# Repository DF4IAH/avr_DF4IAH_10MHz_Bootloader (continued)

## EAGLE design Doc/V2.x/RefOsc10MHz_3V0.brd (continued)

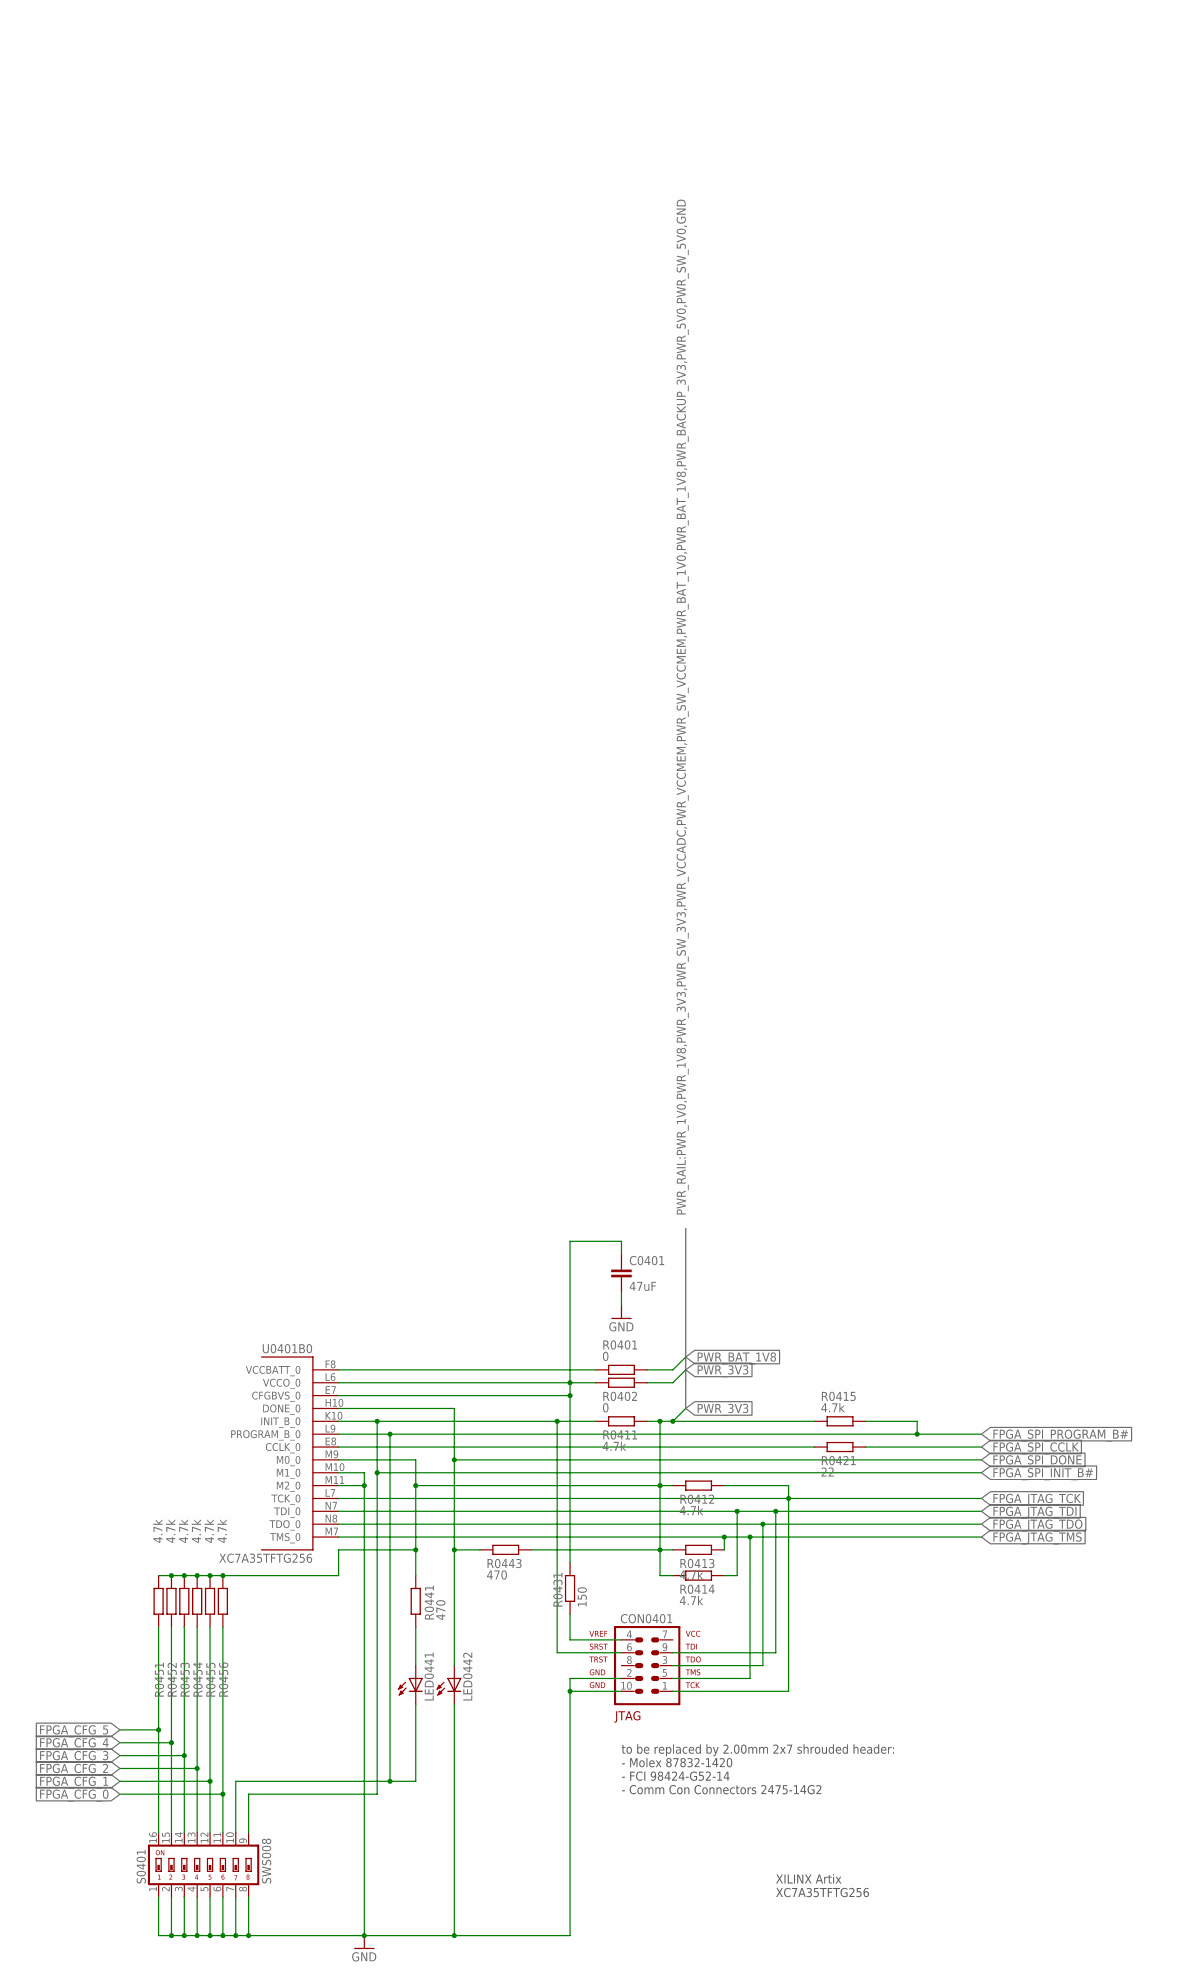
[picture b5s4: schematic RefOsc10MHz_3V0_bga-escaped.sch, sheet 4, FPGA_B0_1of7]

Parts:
C0401: 47uF; C0805
CON0401: AVR-JTAG-10SMD; 2X5SMD
LED0441, LED0442: LED; SMARTLED-TTW
R0401, R0402: 0; R0402
R0411, R0412, R0413, R0414, R0415, R0451, R0452, R0453, R0454, R0455, R0456: 4.7k; R0805
R0421: 22; R0805
R0431: 150; R0805
R0441, R0443: 470; R0805
S0401: SWS008; SMS-008
U0401: XC7A35TFTG256; FTG256_0MM4

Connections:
FPGA_CCLK_INTERN: R0421.1, U0401.E8 (CCLK_0)
FPGA_CFG_0: R0456.1, S0401.11; also elsewhere on the board
FPGA_CFG_1: R0455.1, S0401.12; also elsewhere on the board
FPGA_CFG_2: R0454.1, S0401.13; also elsewhere on the board
FPGA_CFG_3: R0453.1, S0401.14; also elsewhere on the board
FPGA_CFG_4: R0452.1, S0401.15; also elsewhere on the board
FPGA_CFG_5: R0451.1, S0401.16; also elsewhere on the board
FPGA_JTAG_TCK: CON0401.1, R0412.2, U0401.L7 (TCK_0)
FPGA_JTAG_TDI: CON0401.9, R0414.2, U0401.N7 (TDI_0)
FPGA_JTAG_TDO: CON0401.3, U0401.N8 (TDO_0)
FPGA_JTAG_TMS: CON0401.5, R0413.2, U0401.M7 (TMS_0)
FPGA_SPI_CCLK: R0421.2; also elsewhere on the board
FPGA_SPI_DONE: LED0442.A@1 (A), R0443.1, U0401.H10 (DONE_0)
FPGA_SPI_INIT_B#: CON0401.6, R0411.1, S0401.9, U0401.K10 (INIT_B_0)
FPGA_SPI_PROGRAM_B#: LED0441.C@1 (C), R0415.2, S0401.10, U0401.L9 (PROGRAM_B_0)
FPGA_VCCBATT: R0401.1, U0401.F8 (VCCBATT_0)
FPGA_VCCO_0: C0401.1, R0402.1, R0431.2, U0401.E7 (CFGBVS_0), U0401.L6 (VCCO_0)
GND: C0401.2, CON0401.2, CON0401.10, LED0442.C@1 (C), S0401.1, S0401.2, S0401.3, S0401.4, S0401.5, S0401.6, S0401.7, S0401.8, U0401.M10 (M1_0), U0401.M11 (M2_0); also elsewhere on the board
unnamed: LED0441.A@1 (A), R0441.1
unnamed: CON0401.4, R0431.1
PWR_3V3: R0402.2, R0411.2, R0412.1, R0413.1, R0414.1, R0415.1, R0441.2, R0443.2, R0451.2, R0452.2, R0453.2, R0454.2, R0455.2, R0456.2, U0401.M9 (M0_0); also elsewhere on the board
PWR_BAT_1V8: R0401.2; also elsewhere on the board

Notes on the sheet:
XILINX Artix XC7A35TFTG256
to be replaced by 2.00mm 2x7 shrouded header: - Molex 87832-1420 - FCI 98424-G52-14 - Comm Con Connectors 2475-14G2

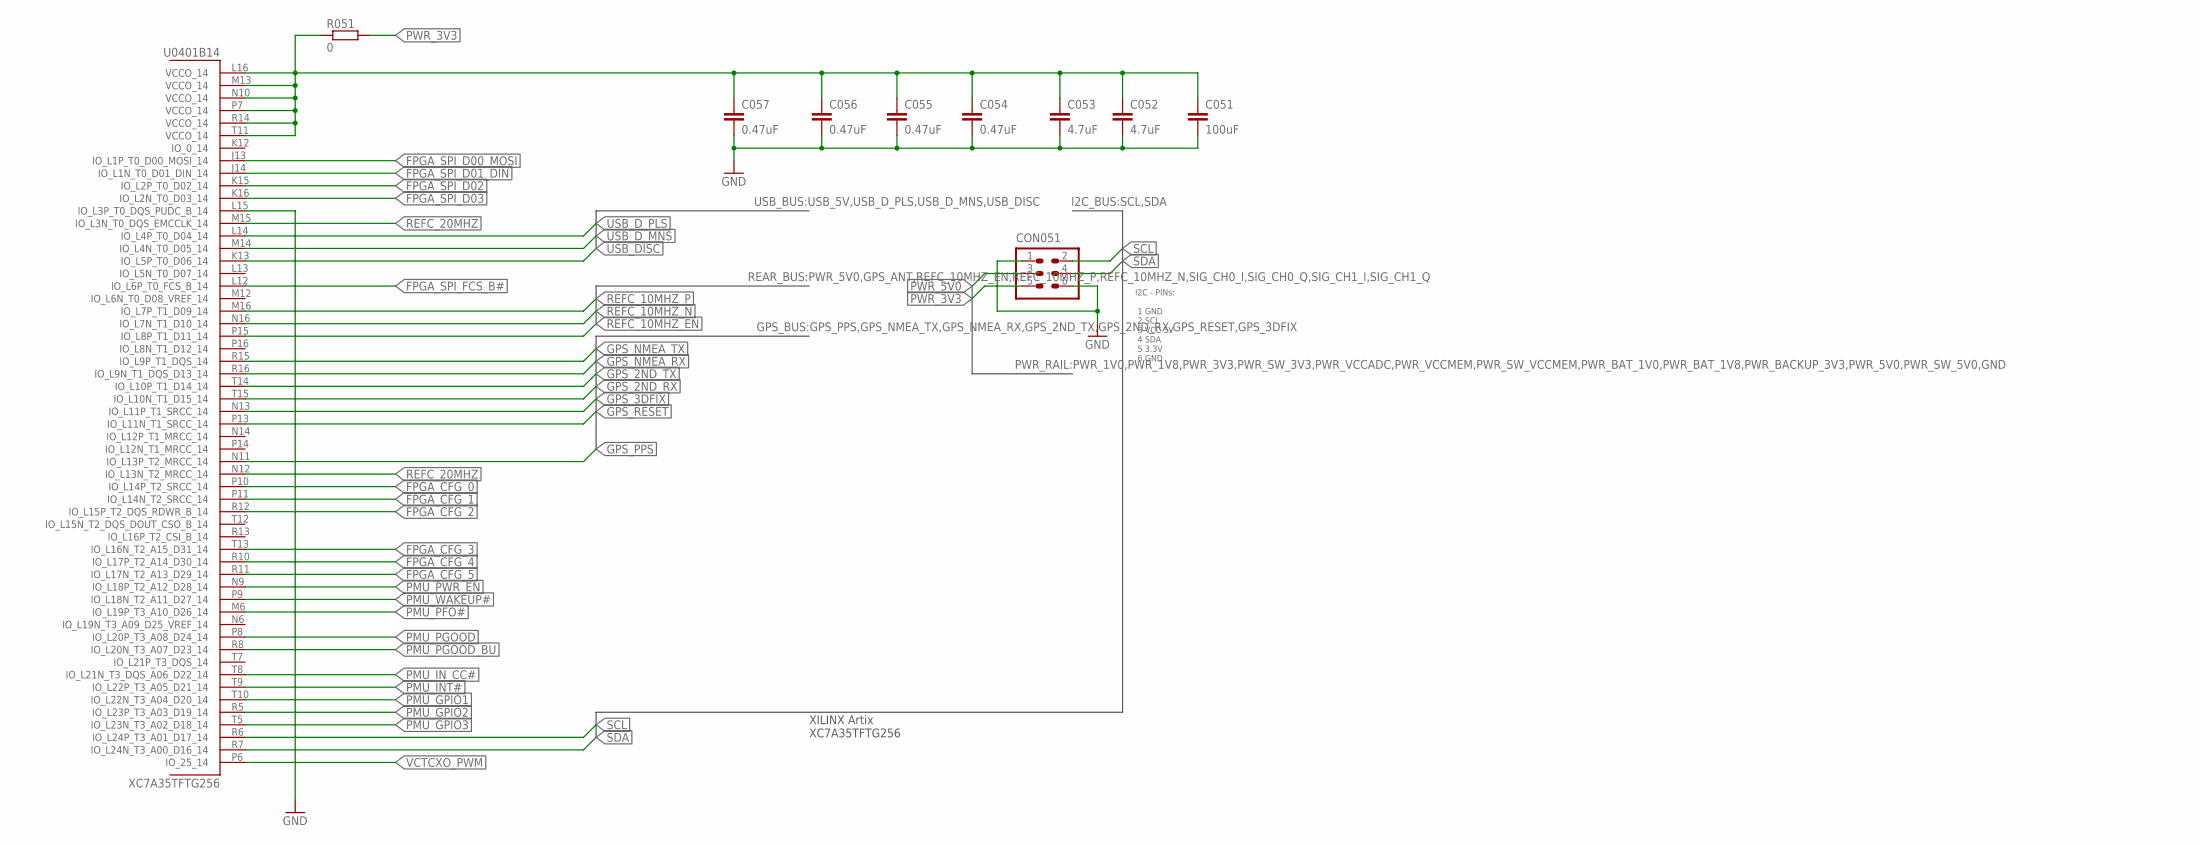
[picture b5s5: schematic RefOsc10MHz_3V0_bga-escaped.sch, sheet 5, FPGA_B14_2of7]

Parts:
C051: 100uF; C1206
C052, C053: 4.7uF; C0402
C054, C055, C056, C057: 0.47uF; C0402
CON051: HEADER-2X3SMD; 2X03SMD
R051: 0; R0402
U0401: XC7A35TFTG256; FTG256_0MM4

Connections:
FPGA_CFG_0: U0401.P10 (IO_L14P_T2_SRCC_14); also elsewhere on the board
FPGA_CFG_1: U0401.P11 (IO_L14N_T2_SRCC_14); also elsewhere on the board
FPGA_CFG_2: U0401.R12 (IO_L15P_T2_DQS_RDWR_B_14); also elsewhere on the board
FPGA_CFG_3: U0401.T13 (IO_L16N_T2_A15_D31_14); also elsewhere on the board
FPGA_CFG_4: U0401.R10 (IO_L17P_T2_A14_D30_14); also elsewhere on the board
FPGA_CFG_5: U0401.R11 (IO_L17N_T2_A13_D29_14); also elsewhere on the board
FPGA_SPI_D00_MOSI: U0401.J13 (IO_L1P_T0_D00_MOSI_14); also elsewhere on the board
FPGA_SPI_D01_DIN: U0401.J14 (IO_L1N_T0_D01_DIN_14); also elsewhere on the board
FPGA_SPI_D02: U0401.K15 (IO_L2P_T0_D02_14); also elsewhere on the board
FPGA_SPI_D03: U0401.K16 (IO_L2N_T0_D03_14); also elsewhere on the board
FPGA_SPI_FCS_B#: U0401.L12 (IO_L6P_T0_FCS_B_14); also elsewhere on the board
FPGA_VCCO_14: C051.1, C052.1, C053.1, C054.1, C055.1, C056.1, C057.1, R051.1, U0401.L16 (VCCO_14), U0401.M13 (VCCO_14), U0401.N10 (VCCO_14), U0401.P7 (VCCO_14), U0401.R14 (VCCO_14), U0401.T11 (VCCO_14)
GND: C051.2, C052.2, C053.2, C054.2, C055.2, C056.2, C057.2, CON051.1, CON051.6, U0401.L15 (IO_L3P_T0_DQS_PUDC_B_14); also elsewhere on the board
GPS_2ND_RX: U0401.T15 (IO_L10N_T1_D15_14)
GPS_2ND_TX: U0401.T14 (IO_L10P_T1_D14_14)
GPS_3DFIX: U0401.N13 (IO_L11P_T1_SRCC_14)
GPS_NMEA_RX: U0401.R16 (IO_L9N_T1_DQS_D13_14); also elsewhere on the board
GPS_NMEA_TX: U0401.R15 (IO_L9P_T1_DQS_14); also elsewhere on the board
GPS_PPS: U0401.N11 (IO_L13P_T2_MRCC_14); also elsewhere on the board
GPS_RESET: U0401.P13 (IO_L11N_T1_SRCC_14); also elsewhere on the board
PMU_GPIO1: U0401.T10 (IO_L22N_T3_A04_D20_14); also elsewhere on the board
PMU_GPIO2: U0401.R5 (IO_L23P_T3_A03_D19_14); also elsewhere on the board
PMU_GPIO3: U0401.T5 (IO_L23N_T3_A02_D18_14); also elsewhere on the board
PMU_INT#: U0401.T9 (IO_L22P_T3_A05_D21_14); also elsewhere on the board
PMU_IN_CC#: U0401.T8 (IO_L21N_T3_DQS_A06_D22_14); also elsewhere on the board
PMU_PFO#: U0401.M6 (IO_L19P_T3_A10_D26_14); also elsewhere on the board
PMU_PGOOD: U0401.P8 (IO_L20P_T3_A08_D24_14); also elsewhere on the board
PMU_PGOOD_BU: U0401.R8 (IO_L20N_T3_A07_D23_14); also elsewhere on the board
PMU_PWR_EN: U0401.N9 (IO_L18P_T2_A12_D28_14); also elsewhere on the board
PMU_WAKEUP#: U0401.P9 (IO_L18N_T2_A11_D27_14); also elsewhere on the board
PWR_3V3: CON051.5, R051.2; also elsewhere on the board
PWR_5V0: CON051.3; also elsewhere on the board
REFC_10MHZ_EN: U0401.P15 (IO_L8P_T1_D11_14); also elsewhere on the board
REFC_10MHZ_N: U0401.N16 (IO_L7N_T1_D10_14); also elsewhere on the board
REFC_10MHZ_P: U0401.M16 (IO_L7P_T1_D09_14); also elsewhere on the board
REFC_20MHZ: U0401.M15 (IO_L3N_T0_DQS_EMCCLK_14), U0401.N12 (IO_L13N_T2_MRCC_14); also elsewhere on the board
SCL: CON051.2, U0401.R6 (IO_L24P_T3_A01_D17_14); also elsewhere on the board
SDA: CON051.4, U0401.R7 (IO_L24N_T3_A00_D16_14); also elsewhere on the board
USB_DISC: U0401.K13 (IO_L5P_T0_D06_14); also elsewhere on the board
USB_D_MNS: U0401.M14 (IO_L4N_T0_D05_14); also elsewhere on the board
USB_D_PLS: U0401.L14 (IO_L4P_T0_D04_14); also elsewhere on the board
VCTCXO_PWM: U0401.P6 (IO_25_14); also elsewhere on the board

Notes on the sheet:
I2C - PINs: 1 GND 2 SCL 3 VCC 5V 4 SDA 5 3.3V 6 GND
XILINX Artix XC7A35TFTG256

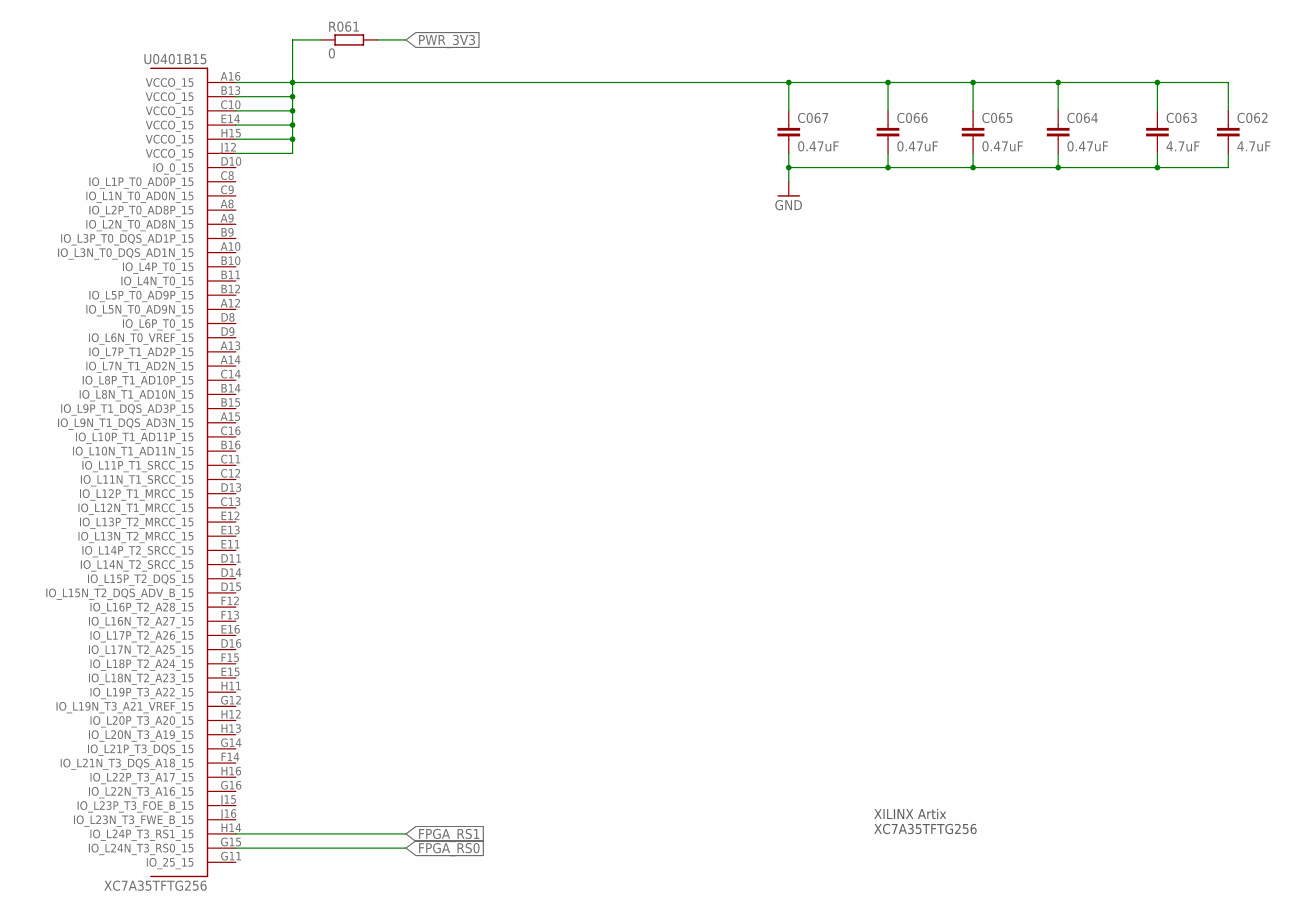
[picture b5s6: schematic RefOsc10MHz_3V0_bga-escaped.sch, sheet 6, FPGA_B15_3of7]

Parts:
C062, C063: 4.7uF; C0402
C064, C065, C066, C067: 0.47uF; C0402
R061: 0; R0402
U0401: XC7A35TFTG256; FTG256_0MM4

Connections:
FPGA_RS0: U0401.G15 (IO_L24N_T3_RS0_15)
FPGA_RS1: U0401.H14 (IO_L24P_T3_RS1_15)
FPGA_VCCO_15: C062.1, C063.1, C064.1, C065.1, C066.1, C067.1, R061.1, U0401.A16 (VCCO_15), U0401.B13 (VCCO_15), U0401.C10 (VCCO_15), U0401.E14 (VCCO_15), U0401.H15 (VCCO_15), U0401.J12 (VCCO_15)
GND: C062.2, C063.2, C064.2, C065.2, C066.2, C067.2; also elsewhere on the board
PWR_3V3: R061.2; also elsewhere on the board

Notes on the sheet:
XILINX Artix XC7A35TFTG256

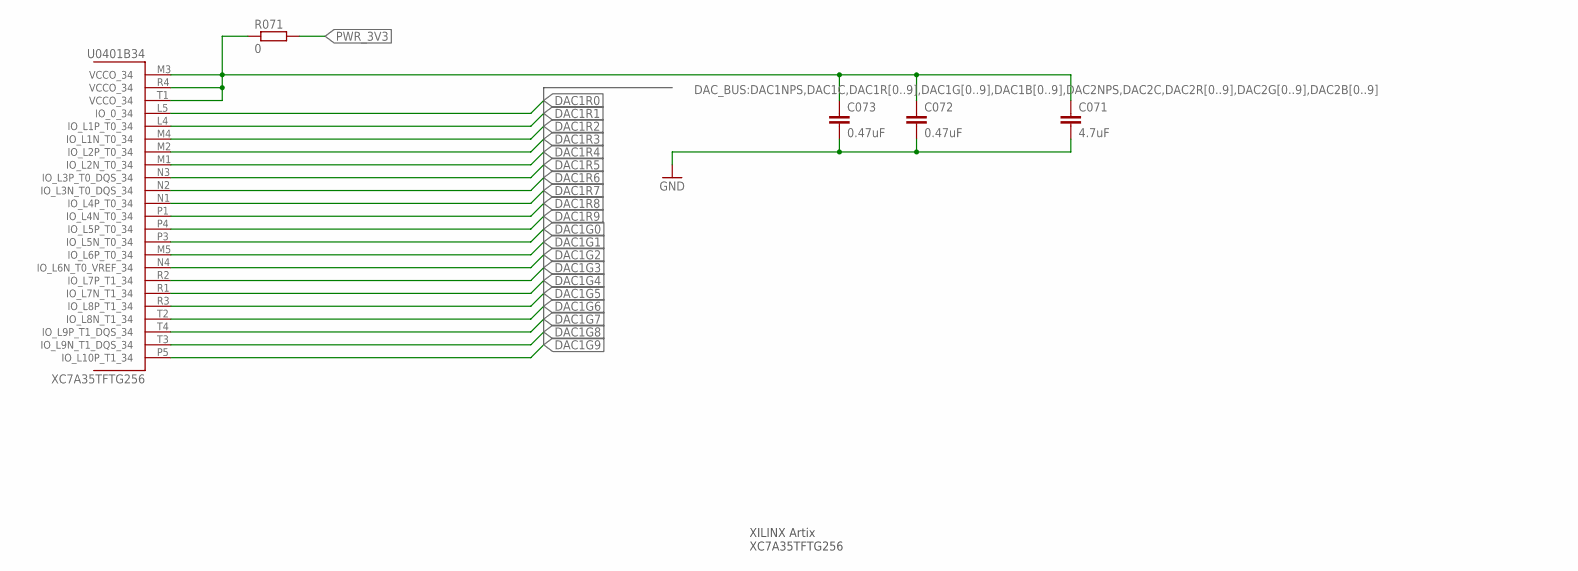
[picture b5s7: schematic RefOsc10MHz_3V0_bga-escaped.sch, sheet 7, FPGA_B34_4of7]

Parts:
C071: 4.7uF; C0402
C072, C073: 0.47uF; C0402
R071: 0; R0402
U0401: XC7A35TFTG256; FTG256_0MM4

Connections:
DAC1G0: U0401.P3 (IO_L5N_T0_34)
DAC1G1: U0401.M5 (IO_L6P_T0_34)
DAC1G2: U0401.N4 (IO_L6N_T0_VREF_34)
DAC1G3: U0401.R2 (IO_L7P_T1_34)
DAC1G4: U0401.R1 (IO_L7N_T1_34)
DAC1G5: U0401.R3 (IO_L8P_T1_34)
DAC1G6: U0401.T2 (IO_L8N_T1_34)
DAC1G7: U0401.T4 (IO_L9P_T1_DQS_34)
DAC1G8: U0401.T3 (IO_L9N_T1_DQS_34)
DAC1G9: U0401.P5 (IO_L10P_T1_34)
DAC1R0: U0401.L5 (IO_0_34)
DAC1R1: U0401.L4 (IO_L1P_T0_34)
DAC1R2: U0401.M4 (IO_L1N_T0_34)
DAC1R3: U0401.M2 (IO_L2P_T0_34)
DAC1R4: U0401.M1 (IO_L2N_T0_34)
DAC1R5: U0401.N3 (IO_L3P_T0_DQS_34)
DAC1R6: U0401.N2 (IO_L3N_T0_DQS_34)
DAC1R7: U0401.N1 (IO_L4P_T0_34)
DAC1R8: U0401.P1 (IO_L4N_T0_34)
DAC1R9: U0401.P4 (IO_L5P_T0_34)
FPGA_VCCO_34: C071.1, C072.1, C073.1, R071.1, U0401.M3 (VCCO_34), U0401.R4 (VCCO_34), U0401.T1 (VCCO_34)
GND: C071.2, C072.2, C073.2; also elsewhere on the board
PWR_3V3: R071.2; also elsewhere on the board

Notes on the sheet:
XILINX Artix XC7A35TFTG256

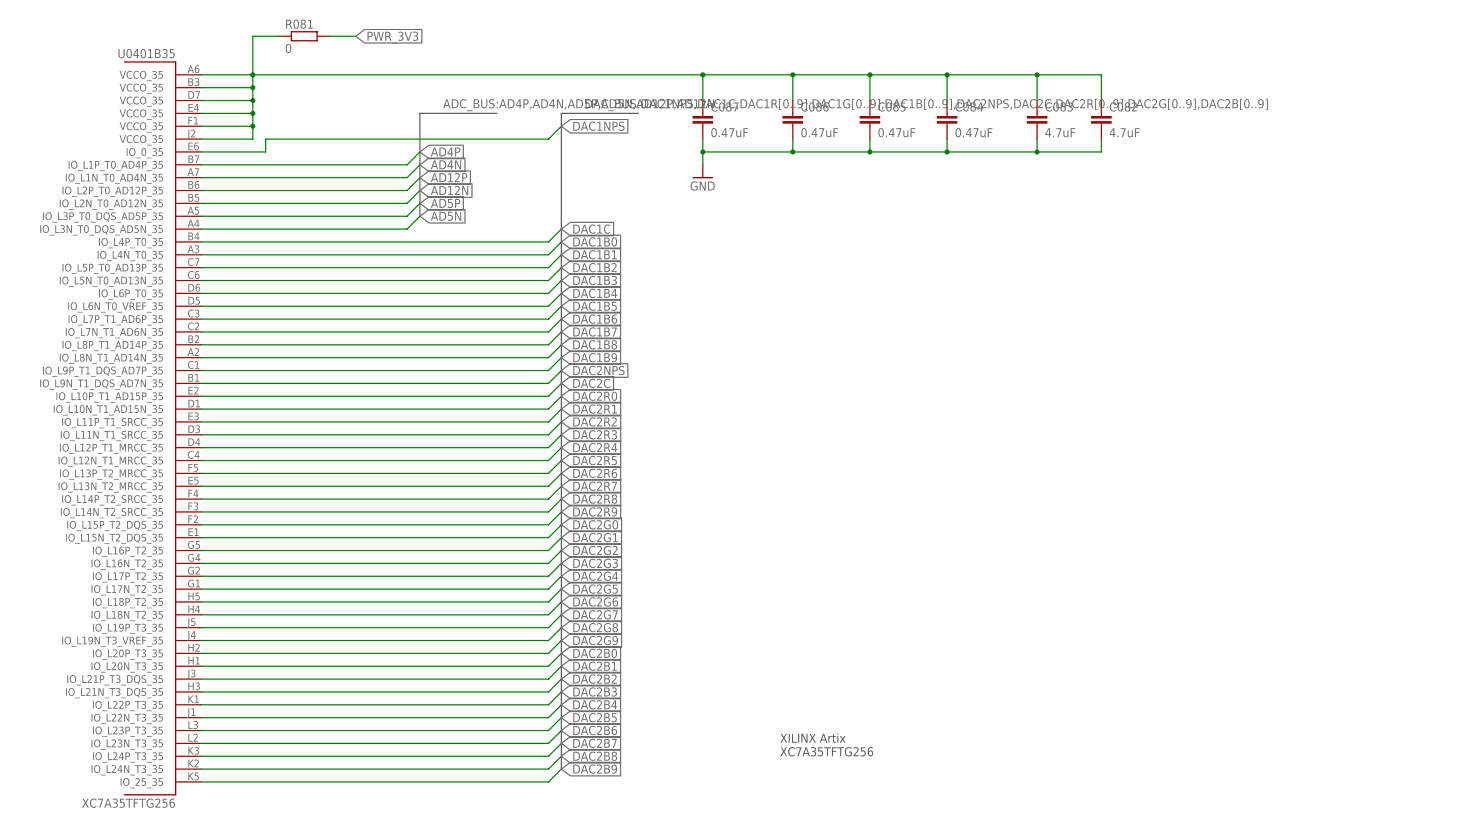
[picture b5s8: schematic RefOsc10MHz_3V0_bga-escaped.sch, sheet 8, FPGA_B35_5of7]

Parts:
C082, C083: 4.7uF; C0402
C084, C085, C086, C087: 0.47uF; C0402
R081: 0; R0402
U0401: XC7A35TFTG256; FTG256_0MM4

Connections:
AD4N: U0401.A7 (IO_L1N_T0_AD4N_35)
AD4P: U0401.B7 (IO_L1P_T0_AD4P_35)
AD5N: U0401.A4 (IO_L3N_T0_DQS_AD5N_35)
AD5P: U0401.A5 (IO_L3P_T0_DQS_AD5P_35)
AD12N: U0401.B5 (IO_L2N_T0_AD12N_35)
AD12P: U0401.B6 (IO_L2P_T0_AD12P_35)
DAC1B0: U0401.A3 (IO_L4N_T0_35)
DAC1B1: U0401.C7 (IO_L5P_T0_AD13P_35)
DAC1B2: U0401.C6 (IO_L5N_T0_AD13N_35)
DAC1B3: U0401.D6 (IO_L6P_T0_35)
DAC1B4: U0401.D5 (IO_L6N_T0_VREF_35)
DAC1B5: U0401.C3 (IO_L7P_T1_AD6P_35)
DAC1B6: U0401.C2 (IO_L7N_T1_AD6N_35)
DAC1B7: U0401.B2 (IO_L8P_T1_AD14P_35)
DAC1B8: U0401.A2 (IO_L8N_T1_AD14N_35)
DAC1B9: U0401.C1 (IO_L9P_T1_DQS_AD7P_35)
DAC1C: U0401.B4 (IO_L4P_T0_35)
DAC1NPS: U0401.E6 (IO_0_35)
DAC2B0: U0401.H1 (IO_L20N_T3_35)
DAC2B1: U0401.J3 (IO_L21P_T3_DQS_35)
DAC2B2: U0401.H3 (IO_L21N_T3_DQS_35)
DAC2B3: U0401.K1 (IO_L22P_T3_35)
DAC2B4: U0401.J1 (IO_L22N_T3_35)
DAC2B5: U0401.L3 (IO_L23P_T3_35)
DAC2B6: U0401.L2 (IO_L23N_T3_35)
DAC2B7: U0401.K3 (IO_L24P_T3_35)
DAC2B8: U0401.K2 (IO_L24N_T3_35)
DAC2B9: U0401.K5 (IO_25_35)
DAC2C: U0401.E2 (IO_L10P_T1_AD15P_35)
DAC2G0: U0401.E1 (IO_L15N_T2_DQS_35)
DAC2G1: U0401.G5 (IO_L16P_T2_35)
DAC2G2: U0401.G4 (IO_L16N_T2_35)
DAC2G3: U0401.G2 (IO_L17P_T2_35)
DAC2G4: U0401.G1 (IO_L17N_T2_35)
DAC2G5: U0401.H5 (IO_L18P_T2_35)
DAC2G6: U0401.H4 (IO_L18N_T2_35)
DAC2G7: U0401.J5 (IO_L19P_T3_35)
DAC2G8: U0401.J4 (IO_L19N_T3_VREF_35)
DAC2G9: U0401.H2 (IO_L20P_T3_35)
DAC2NPS: U0401.B1 (IO_L9N_T1_DQS_AD7N_35)
DAC2R0: U0401.D1 (IO_L10N_T1_AD15N_35)
DAC2R1: U0401.E3 (IO_L11P_T1_SRCC_35)
DAC2R2: U0401.D3 (IO_L11N_T1_SRCC_35)
DAC2R3: U0401.D4 (IO_L12P_T1_MRCC_35)
DAC2R4: U0401.C4 (IO_L12N_T1_MRCC_35)
DAC2R5: U0401.F5 (IO_L13P_T2_MRCC_35)
DAC2R6: U0401.E5 (IO_L13N_T2_MRCC_35)
DAC2R7: U0401.F4 (IO_L14P_T2_SRCC_35)
DAC2R8: U0401.F3 (IO_L14N_T2_SRCC_35)
DAC2R9: U0401.F2 (IO_L15P_T2_DQS_35)
FPGA_VCCO_35: C082.1, C083.1, C084.1, C085.1, C086.1, C087.1, R081.1, U0401.A6 (VCCO_35), U0401.B3 (VCCO_35), U0401.D7 (VCCO_35), U0401.E4 (VCCO_35), U0401.F1 (VCCO_35), U0401.J2 (VCCO_35)
GND: C082.2, C083.2, C084.2, C085.2, C086.2, C087.2; also elsewhere on the board
PWR_3V3: R081.2; also elsewhere on the board

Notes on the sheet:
XILINX Artix XC7A35TFTG256

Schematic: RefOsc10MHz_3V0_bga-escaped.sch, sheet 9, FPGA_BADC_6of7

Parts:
C091: 4.7uF; C0402
C092: 0.47uF; C0402
R091: 0; R0402
U0401: XC7A35TFTG256; FTG256_0MM4

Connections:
AGND: U0401.G7 (GNDADC_0), U0401.H7 (VREFN_0), U0401.J7 (VN_0); also elsewhere on the board
FPGA_ADC_VP_0: U0401.H8 (VP_0)
FPGA_VCCADC_0: C091.1, C092.1, R091.1, U0401.G8 (VCCADC_0)
GND: C091.2, C092.2; also elsewhere on the board
PWR_1V25_PREC: U0401.J8 (VREFP_0)
PWR_VCCADC: R091.2; also elsewhere on the board

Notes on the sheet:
XILINX Artix XC7A35TFTG256

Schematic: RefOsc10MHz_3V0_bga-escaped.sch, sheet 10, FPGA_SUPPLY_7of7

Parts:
C1001: 100uF; C1206
C1002, C1003, C1022, C1023: 4.7uF; C0402
C1004, C1005, C1006, C1012, C1024, C1025, C1026: 0.47uF; C0402
C1011, C1021: 47uF; C0805
R101, R102, R103, R104, R105: 0; R0402
U0401: XC7A35TFTG256; FTG256_0MM4

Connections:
FPGA_DXN_0: R105.1, U0401.K7 (DXN_0)
FPGA_DXP_0: R104.1, U0401.K8 (DXP_0)
FPGA_VCCAUX: C1021.1, C1022.1, C1023.1, C1024.1, C1025.1, C1026.1, R103.1, U0401.G10 (VCCAUX), U0401.J10 (VCCAUX), U0401.K11 (VCCAUX), U0401.L10 (VCCAUX)
FPGA_VCCBRAM: C1011.1, C1012.1, R102.1, U0401.E10 (VCCBRAM), U0401.F11 (VCCBRAM)
FPGA_VCCINT: C1001.1, C1002.1, C1003.1, C1004.1, C1005.1, C1006.1, R101.1, U0401.F7 (VCCINT), U0401.F9 (VCCINT), U0401.G6 (VCCINT), U0401.H9 (VCCINT), U0401.J6 (VCCINT), U0401.K9 (VCCINT), U0401.L8 (VCCINT)
GND: C1001.2, C1002.2, C1003.2, C1004.2, C1005.2, C1006.2, C1011.2, C1012.2, C1021.2, C1022.2, C1023.2, C1024.2, C1025.2, C1026.2, R104.2, R105.2, U0401.A1 (GND), U0401.A11 (GND), U0401.B8 (GND), U0401.C5 (GND), U0401.C15 (GND), U0401.D2 (GND), U0401.D12 (GND), U0401.E9 (GND), U0401.F6 (GND), U0401.F10 (GND), U0401.F16 (GND), U0401.G3 (GND), U0401.G9 (GND), U0401.G13 (GND), U0401.H6 (GND), U0401.J9 (GND), U0401.J11 (GND), U0401.K4 (GND), U0401.K6 (GND), U0401.K14 (GND), U0401.L1 (GND), U0401.L11 (GND), U0401.M8 (GND), U0401.N5 (GND), U0401.N15 (GND), U0401.P2 (GND), U0401.P12 (GND), U0401.R9 (GND), U0401.T6 (GND), U0401.T16 (GND); also elsewhere on the board
PWR_1V0: R101.2, R102.2; also elsewhere on the board
PWR_1V8: R103.2; also elsewhere on the board

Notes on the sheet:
XILINX Artix XC7A35TFTG256

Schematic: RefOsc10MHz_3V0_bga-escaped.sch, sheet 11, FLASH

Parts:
R111: 4.7k; R0805
R112, R113: 100k; R0805
U111: N25Q128A13ESE40F; SOP2-8

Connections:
FPGA_SPI_CCLK: U111.6 (C); also elsewhere on the board
FPGA_SPI_D00_MOSI: U111.5 (DQ0); also elsewhere on the board
FPGA_SPI_D01_DIN: U111.2 (DQ1); also elsewhere on the board
FPGA_SPI_D02: R112.1, U111.3 (W#_VPP_DQ2); also elsewhere on the board
FPGA_SPI_D03: R113.1, U111.7 (HOLD#/DQ3); also elsewhere on the board
FPGA_SPI_FCS_B#: R111.1, U111.1 (S#); also elsewhere on the board
GND: U111.4 (VSS); also elsewhere on the board
PWR_3V3: R111.2, R112.2, R113.2, U111.8 (VDD); also elsewhere on the board

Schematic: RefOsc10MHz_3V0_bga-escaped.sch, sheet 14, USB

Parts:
C141: 47uF; C0805
C142: 100n; C0805
CON141: TYCO-AMP_USBUSB-B_SMT; TYCO-AMP_USB-B_SMT
D141, D142: BZX84-C3V6; TO236
R141, R142: 68; R0805
R143: 1M; R0805
R144: 1.5k; R0805
RP141: 1206L025YR_0.5A; M1206

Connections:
GND: C141.2, C142.2, CON141.4 (GND), D141.A, D142.A, R143.1; also elsewhere on the board
PWR_5V0: C141.1, C142.1, RP141.2; also elsewhere on the board
USB_DISC: R144.2; also elsewhere on the board
USB_D_MIN1: CON141.2 (D-), D142.C, R142.1, R144.1
USB_D_MNS: R142.2; also elsewhere on the board
USB_D_PLS: R141.2; also elsewhere on the board
USB_D_PLS1: CON141.3 (D+), D141.C, R141.1, R143.2
USB_PWR1: CON141.1 (VBUS), RP141.1

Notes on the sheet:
USB-B

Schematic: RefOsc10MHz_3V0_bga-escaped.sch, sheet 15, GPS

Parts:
C151: 100n; C0805
CON151: HEADER-2X5SMD; 2X5SMD
LP151: WE-CBF_300R; L3216C
R151, R152: 100k; R0805
RP151: 1206L012WR_0.1A; M1206
U151: TJ1513MTBD

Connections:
GND: C151.2, CON151.1, CON151.9, CON151.10, U151.6 (GND), U151.17 (GND), U151.20 (GND), U151.22 (GND); also elsewhere on the board
GPS_ANT: LP151.1, U151.21 (RF_IN); also elsewhere on the board
GPS_NMEA_RX: CON151.5, R152.1, U151.5 (RXD1); also elsewhere on the board
GPS_NMEA_TX: CON151.6, U151.4 (TXD1); also elsewhere on the board
GPS_PPS: CON151.7, U151.3 (TIMEPULSE); also elsewhere on the board
GPS_PWR_3V3: C151.1, CON151.4, R151.2, R152.2, RP151.2, U151.13 (VCC)
GPS_RESET: R151.1, U151.11 (RESET); also elsewhere on the board
unnamed: LP151.2, U151.19 (VCC_RF)
PWR_3V3: RP151.1; also elsewhere on the board
PWR_5V0: CON151.3; also elsewhere on the board
PWR_BACKUP_3V3: CON151.2, U151.12 (V_BAKP); also elsewhere on the board

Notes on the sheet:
GPS - PINs: 1 GND 2 V_BAT, Memory Supply, Goldcap 3 VCC 5V 4 V_ANT 5V, fused 5 GPS NMEA RX 6 GPS NMEA TX 7 PPS (1 Hz) 8 Ref. 10 kHz 9 GND 10 GND

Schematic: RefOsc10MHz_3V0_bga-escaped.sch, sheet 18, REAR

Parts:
CON181, CON183, CON184, CON185, CON186: MCX-J-P-X-RA-SM1
CON182: SD-73100-0105; MOLEX_BNC-JACK-50R_SD-73100-0105
R181: 51; R0805
R182, R183: 120; R0805
U181: OPA357; SOT-23-6

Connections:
GND: CON181.2, CON181.3, CON181.4, CON181.5, CON182.2, CON182.3, CON183.2, CON183.3, CON183.4, CON183.5, CON184.2, CON184.3, CON184.4, CON184.5, CON185.2, CON185.3, CON185.4, CON185.5, CON186.2, CON186.3, CON186.4, CON186.5, R182.1, R183.1, U181.2 (V-); also elsewhere on the board
GPS_ANT: CON181.1; also elsewhere on the board
unnamed: R181.1, U181.1 (OUT)
unnamed: CON182.1, R181.2
PWR_5V0: U181.6 (V+); also elsewhere on the board
REFC_10MHZ_EN: U181.5 (ENABLE); also elsewhere on the board
REFC_10MHZ_N: R183.2, U181.4 (-IN); also elsewhere on the board
REFC_10MHZ_P: R182.2, U181.3 (+IN); also elsewhere on the board
SIG_CH0_I: CON183.1
SIG_CH0_Q: CON184.1
SIG_CH1_I: CON185.1
SIG_CH1_Q: CON186.1

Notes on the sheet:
10 MHz RefClk Out
GPS Ant In
CH0 I Out
CH0 Q Out
CH1 I Out
CH1 Q Out

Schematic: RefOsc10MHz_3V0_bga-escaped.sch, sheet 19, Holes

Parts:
H191, H192, H193, H194: MOUNT-PAD-ROUND2.8; 2,8-PAD

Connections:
GND: H191.B2,8, H192.B2,8, H193.B2,8, H194.B2,8; also elsewhere on the board

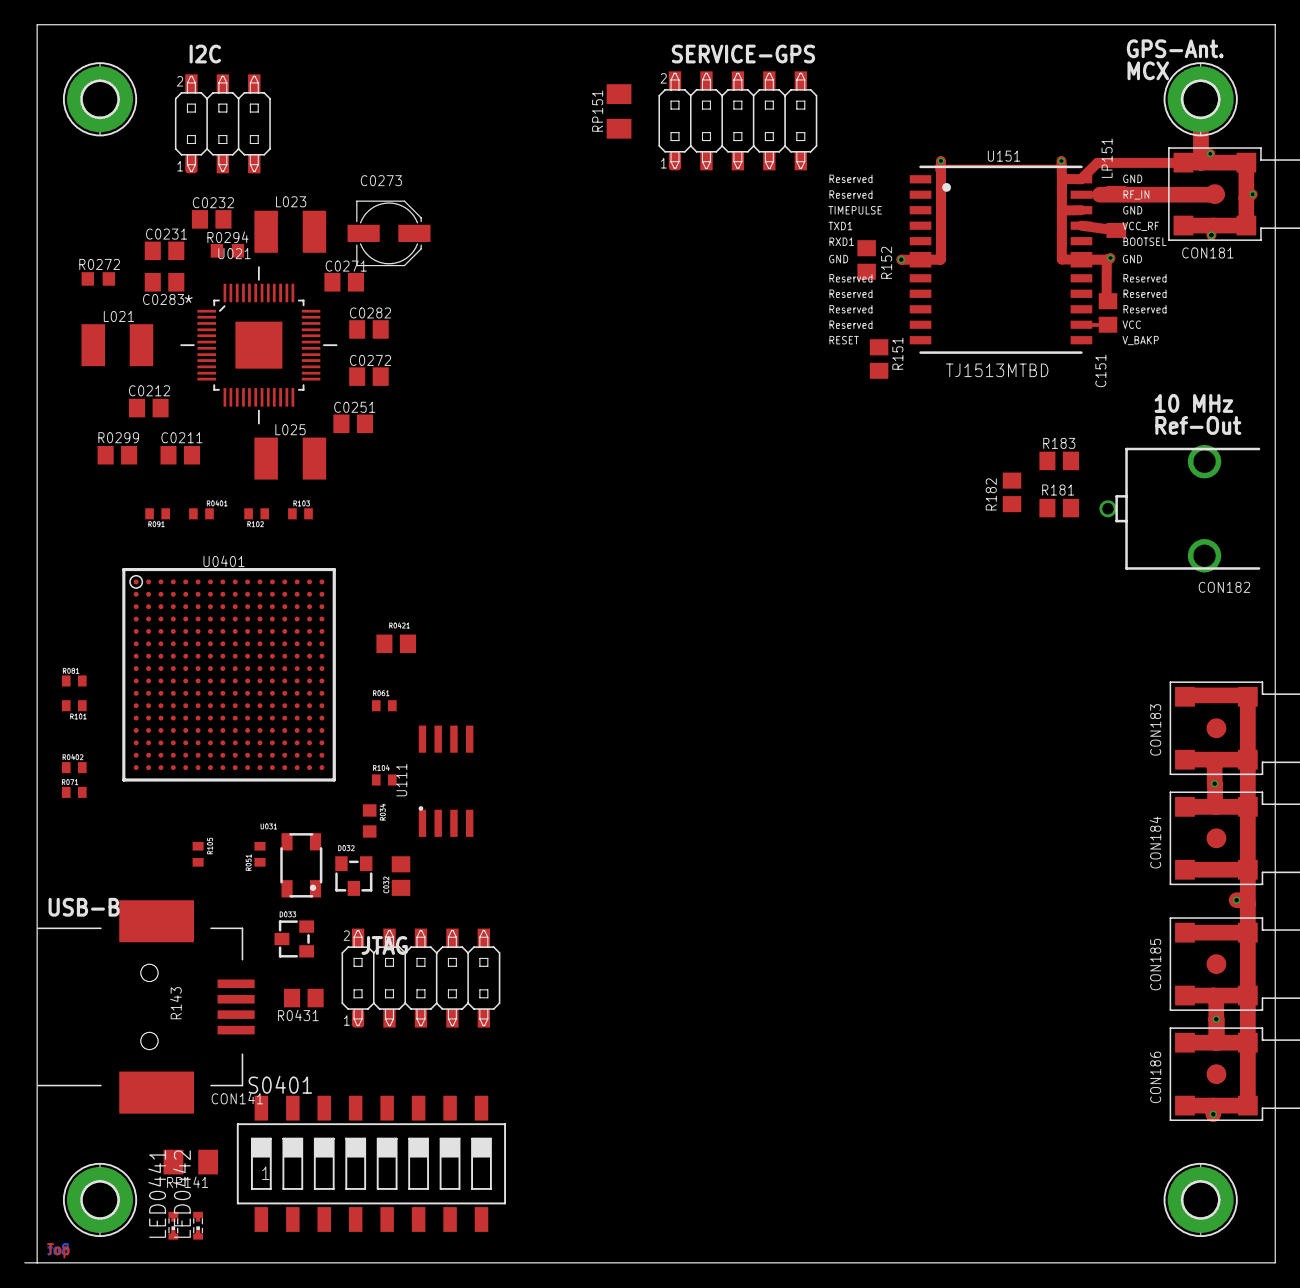
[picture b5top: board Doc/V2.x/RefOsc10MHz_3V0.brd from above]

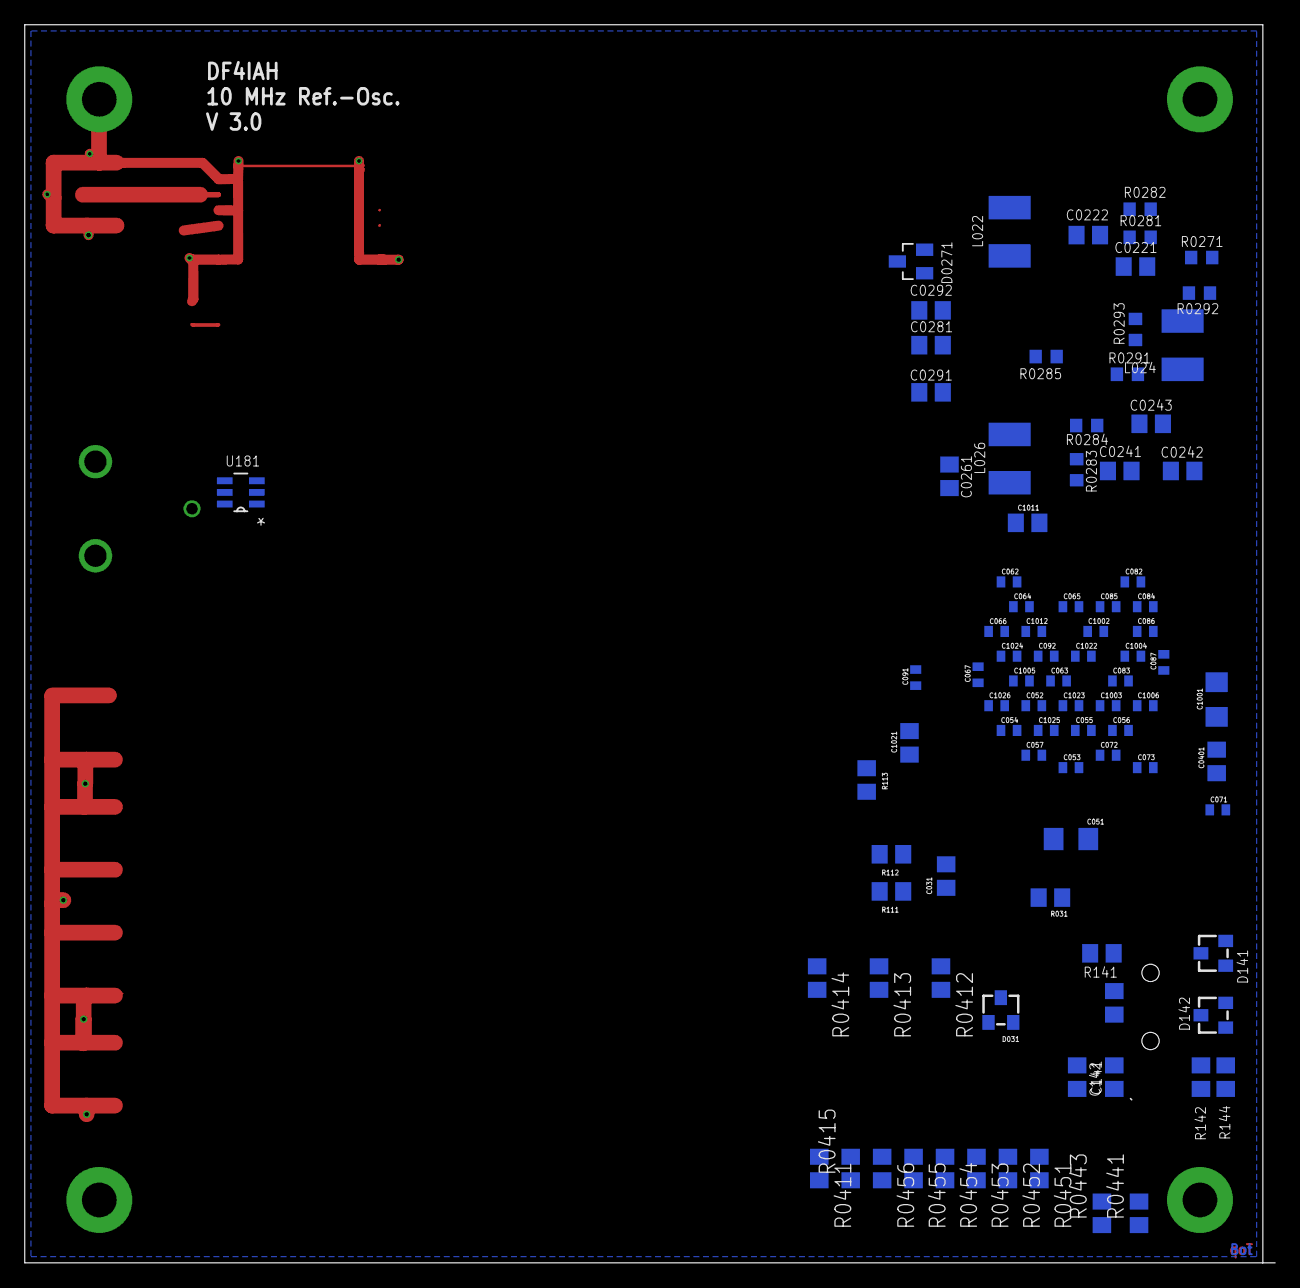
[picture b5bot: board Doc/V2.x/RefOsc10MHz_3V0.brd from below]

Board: 4 copper layers, 101.0 x 100.0 mm, 154 parts (89 on the bottom side), 94 nets.
